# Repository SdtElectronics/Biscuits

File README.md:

# Biscuits 
This repository contains various PCB works for minor projects or auxiliary purposes.

Note: Cloning whole repository for single directory is unnecessary. You can use [DownGit](https://minhaskamal.github.io/DownGit/#/home) to download single directories or file.

## [BBSink](./bbSink/README.md)
USB-PD sink with headers compatible with breadboard. Features a fixed 3.3V supply and one-click voltage selection without incorporating MCUs

## [LCD_Bias_Voltage_Generator](./LCD_Bias_Voltage_Generator/README.md)
Except a 3.3V `DVDD`, LCD panels typically require 4 additional voltages: `AVDD`, `VGH`, `VGL` and `VCOM`. This board employs a simple circuit to generate these 4 voltages from a single 3.3V supply.

## [PCA9685_Breakout](./PCA9685_Breakout/README.md)
Breakout board for PCA9685 I²C to 16-channel PWM controller.

## [BLDC_D28_Drv](./BLDC_D28_Drv/README.md)
Tiny driver stage for mounting on BLDC motors with 28/29mm diameters.

## [CH224Core](./CH224Core/README.md)
Tiny breakout board for CH224K USB-PD sink IC.

## [XPT2046_RTP](./XPT2046_RTP/README.md)
Breakout board for XPT2046 resistive touch screen controller.

## yuyuyu_ant
Antenna for α-wave transmission( XD

## 50P_FPC_FFC_Breakout
Breakout board for FFC/FPC connectors with 50 positions and 0.5mm pitch.

## 40P_FPC_FFC_Breakout
Breakout board for FFC/FPC connectors with 40 positions and 0.5mm pitch.

## 24P_FPC_FFC_Breakout
Breakout board for FFC/FPC connectors with 24 positions and 0.5mm pitch.

## 14P_FPC_FFC_Breakout
Breakout board for FFC/FPC connectors with 14 positions and 0.5mm pitch.

## 9P_FPC_FFC_Breakout
Breakout board for FFC/FPC connectors with 14 positions and 0.5mm or 1mm pitch.

## Licence
All projects contained in this repository, unless otherwise stated, are available under the [CERN OHL-w v2](https://ohwr.org/project/cernohl/wikis/Documents/CERN-OHL-version-2) licence.

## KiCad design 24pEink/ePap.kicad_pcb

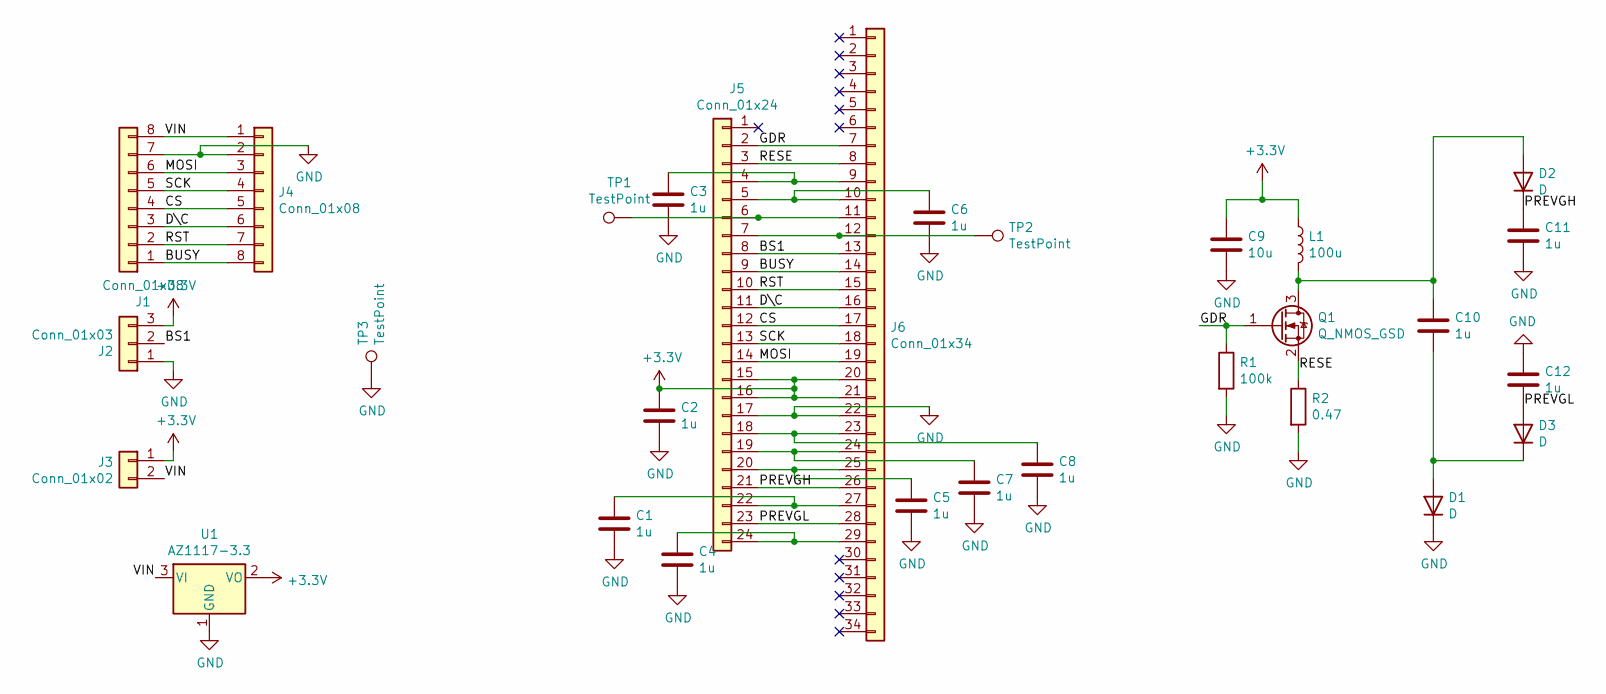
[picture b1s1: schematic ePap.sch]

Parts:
C1, C2, C3, C4, C5, C6, C7, C8, C10, C11, C12: 1u; C_0603_1608Metric_Pad1.05x0.95mm_HandSolder
C9: 10u; C_0603_1608Metric_Pad1.05x0.95mm_HandSolder
D1, D2, D3: D; D_SOD-123
J1: Conn_01x08; TE_0-1734839-8_1x08-1MP_P0.5mm_Horizontal
J2: Conn_01x03; PinHeader_1x03_P2.00mm_Horizontal
J3: Conn_01x02; PinHeader_1x02_P2.00mm_Horizontal
J4: Conn_01x08; PinHeader_1x08_P2.54mm_Vertical
J5: Conn_01x24; TE_2-1734839-4_1x24-1MP_P0.5mm_Horizontal
J6: Conn_01x34; TE_3-1734839-4_1x34-1MP_P0.5mm_Horizontal
L1: 100u; L_Taiyo-Yuden_NR-30xx_HandSoldering
Q1: Q_NMOS_GSD; SOT-23
R1: 100k; R_0805_2012Metric_Pad1.15x1.40mm_HandSolder
R2: 0.47; R_0805_2012Metric_Pad1.15x1.40mm_HandSolder
TP1, TP2: TestPoint; TestPoint_Pad_D1.0mm
TP3: TestPoint; TestPoint_THTPad_D2.5mm_Drill1.2mm
U1: AZ1117-3.3; SOT-223

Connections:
+3V3: C2.1, C9.1, J2.3, J3.1, J5.15, J5.16, J6.20, J6.21, L1.1, U1.2 (VO)
/BS1: J2.2, J5.8, J6.13
/BUSY: J1.1, J4.8, J5.9, J6.14
/CS: J1.4, J4.5, J5.12, J6.17
/D\C: J1.3, J4.6, J5.11, J6.16
/GDR: J5.2, J6.7, Q1.1 (G), R1.1
/MOSI: J1.6, J4.3, J5.14, J6.19
/PREVGH: C11.1, D2.1 (K), J5.21, J6.26
/PREVGL: C12.2, D3.2 (A), J5.23, J6.28
/RESE: J5.3, J6.8, Q1.2 (S), R2.1
/RST: J1.2, J4.7, J5.10, J6.15
/SCK: J1.5, J4.4, J5.13, J6.18
/VIN: J1.8, J3.2, J4.1, U1.3 (VI)
GND: C1.2, C2.2, C3.2, C4.2, C5.2, C6.2, C7.2, C8.2, C9.2, C11.2, C12.1, D1.1 (K), J1.7, J2.1, J4.2, J5.17, J6.22, R1.2, R2.2, TP3.1, U1.1 (GND)
unnamed: C1.1, J5.22, J6.27
unnamed: C3.1, J5.4, J6.9
unnamed: C4.1, J5.24, J6.29
unnamed: C5.1, J5.20, J6.25
unnamed: C6.1, J5.5, J6.10
unnamed: C7.1, J5.19, J6.24
unnamed: C8.1, J5.18, J6.23
unnamed: C10.1, D2.2 (A), L1.2, Q1.3 (D)
unnamed: C10.2, D1.2 (A), D3.1 (K)
unnamed: J5.6, J6.11, TP1.1
unnamed: J5.7, J6.12, TP2.1

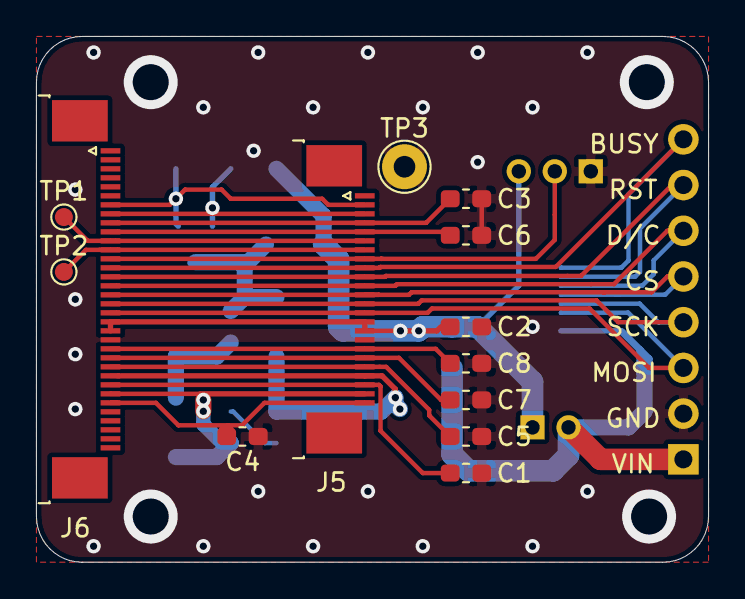
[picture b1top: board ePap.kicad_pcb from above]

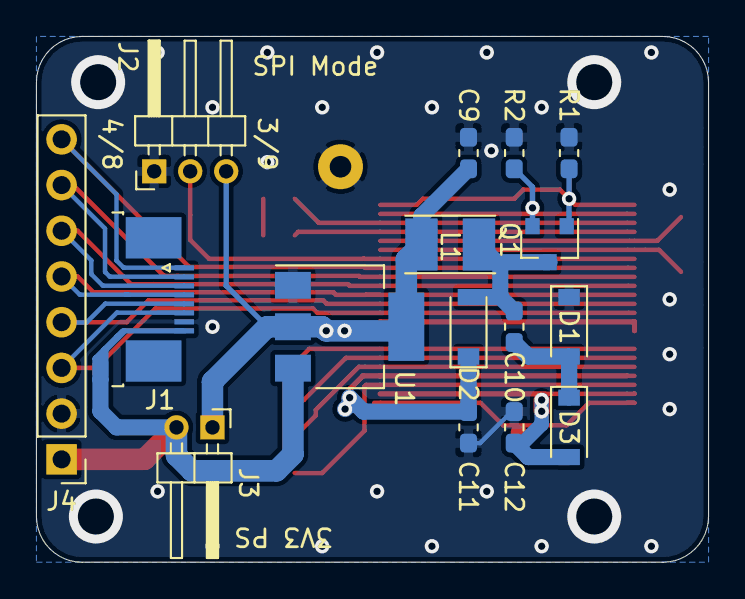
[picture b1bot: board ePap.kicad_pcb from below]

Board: 2 copper layers, 37.3 x 29.2 mm, 29 parts (16 on the bottom side), 25 nets.

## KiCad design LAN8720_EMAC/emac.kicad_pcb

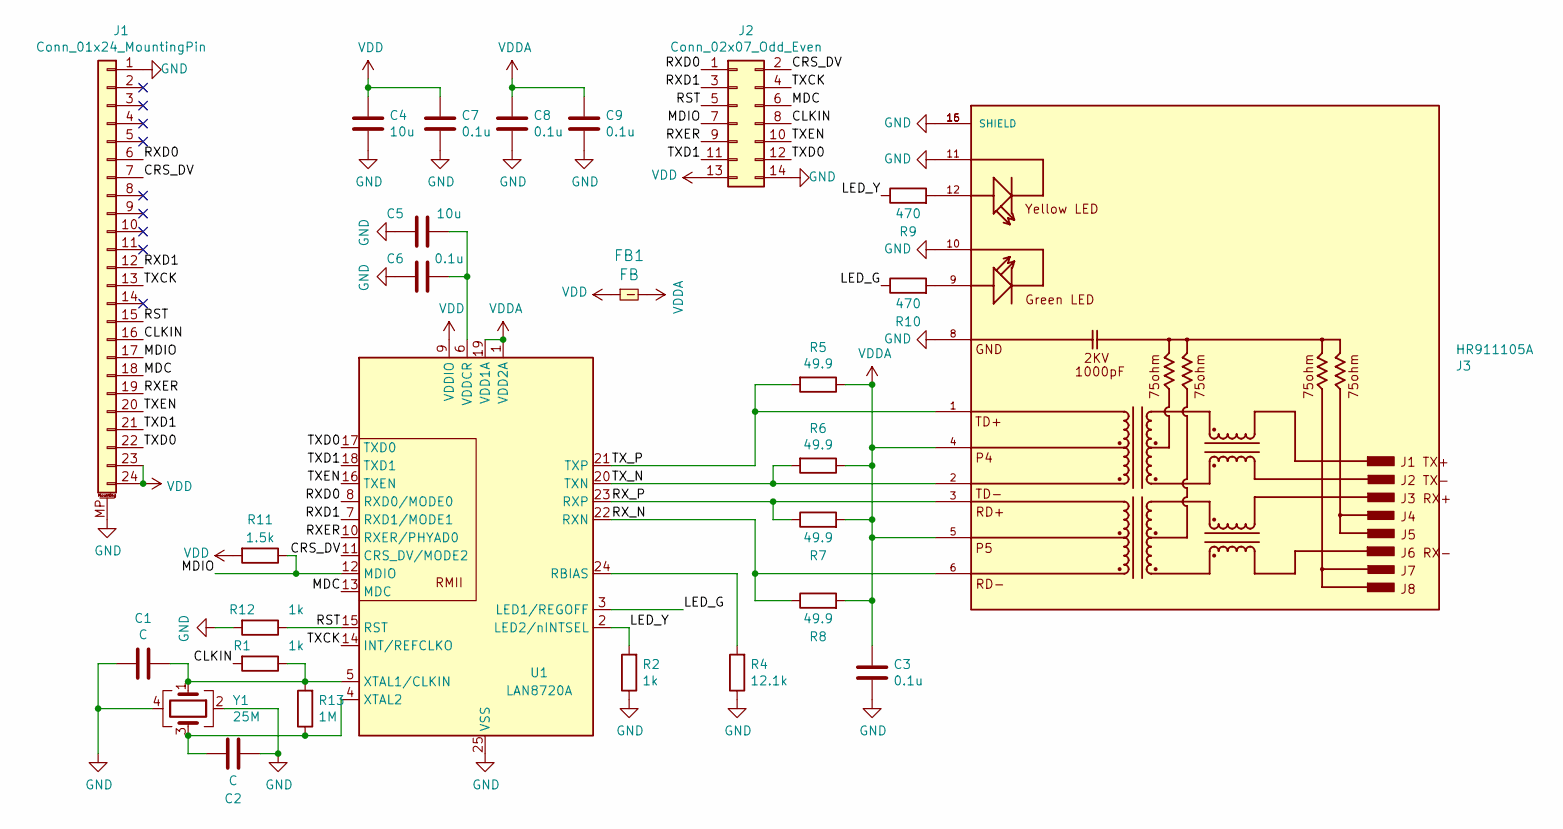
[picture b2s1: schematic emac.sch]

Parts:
C1, C2: C; C_0603_1608Metric
C3, C6, C7, C8, C9: 0.1u; C_0603_1608Metric
C4, C5: 10u; C_0603_1608Metric
FB1: FB; L_0603_1608Metric
J1: Conn_01x24_MountingPin; TE_2-1734839-4_1x24-1MP_P0.5mm_Horizontal
J2: Conn_02x07_Odd_Even; PinHeader_2x07_P2.54mm_Vertical
J3: HR911105A; HANRUN_HR911105A; PARTREV A
R1, R2, R12: 1k; R_0603_1608Metric
R4: 12.1k; R_0603_1608Metric
R5, R6, R7, R8: 49.9; R_0603_1608Metric
R9, R10: 470; R_0603_1608Metric
R11: 1.5k; R_0603_1608Metric
R13: 1M; R_0603_1608Metric
U1: LAN8720A; QFN-24-1EP_4x4mm_P0.5mm_EP2.6x2.6mm
Y1: 25M; Crystal_SMD_3225-4Pin_3.2x2.5mm

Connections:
/CLKIN: J1.16, J2.8, R1.2
/CRS_DV: J1.7, J2.2, U1.11 (CRS_DV/MODE2)
/LED_G: R10.1, U1.3 (LED1/REGOFF)
/LED_Y: R2.2, R9.1, U1.2 (LED2/nINTSEL)
/MDC: J1.18, J2.6, U1.13 (MDC)
/MDIO: J1.17, J2.7, R11.1, U1.12 (MDIO)
/RST: J1.15, J2.5, R12.1, U1.15 (RST)
/RXD0: J1.6, J2.1, U1.8 (RXD0/MODE0)
/RXD1: J1.12, J2.3, U1.7 (RXD1/MODE1)
/RXER: J1.19, J2.9, U1.10 (RXER/PHYAD0)
/RX_N: J3.6, R8.1, U1.22 (RXN)
/RX_P: J3.3, R7.1, U1.23 (RXP)
/TXCK: J1.13, J2.4, U1.14 (INT/REFCLKO)
/TXD0: J1.22, J2.12, U1.17 (TXD0)
/TXD1: J1.21, J2.11, U1.18 (TXD1)
/TXEN: J1.20, J2.10, U1.16 (TXEN)
/TX_N: J3.2, R6.2, U1.20 (TXN)
/TX_P: J3.1, R5.2, U1.21 (TXP)
GND: C1.1, C2.2, C3.2, C4.2, C5.1, C6.1, C7.2, C8.2, C9.2, J1.1, J1.MP (MountPin), J2.14, J3.8, J3.10, J3.11, J3.15 (SHIELD), J3.16 (SHIELD), R2.1, R4.1, R12.2, U1.25 (VSS), Y1.2, Y1.4
unnamed: C1.2, R1.1, R13.2, U1.5 (XTAL1/CLKIN), Y1.1
unnamed: C2.1, R13.1, U1.4 (XTAL2), Y1.3
unnamed: C5.2, C6.2, U1.6 (VDDCR)
unnamed: J3.9, R10.2
unnamed: J3.12, R9.2
unnamed: R4.2, U1.24 (RBIAS)
VDD: C4.1, C7.1, FB1.1, J1.23, J1.24, J2.13, R11.2, U1.9 (VDDIO)
VDDA: C3.1, C8.1, C9.1, FB1.2, J3.4, J3.5, R5.1, R6.1, R7.2, R8.2, U1.1 (VDD2A), U1.19 (VDD1A)

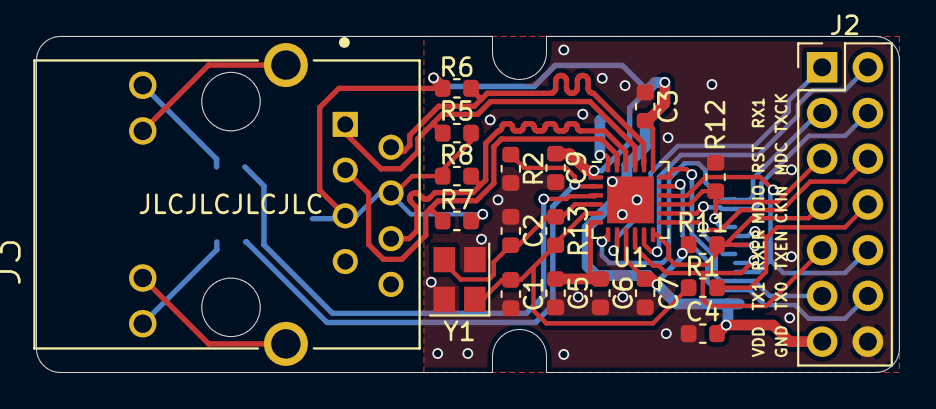
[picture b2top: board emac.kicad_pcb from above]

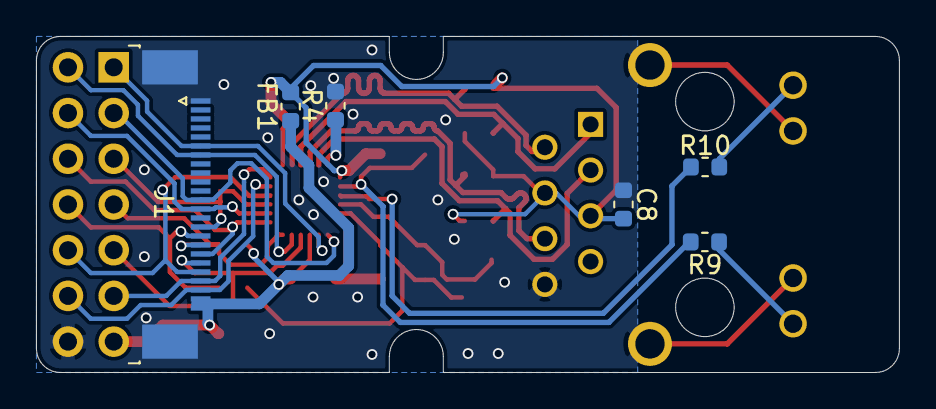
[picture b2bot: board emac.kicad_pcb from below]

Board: 2 copper layers, 47.9 x 18.7 mm, 27 parts (6 on the bottom side), 27 nets.

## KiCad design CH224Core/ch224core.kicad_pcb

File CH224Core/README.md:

# CH224Core
Tiny breakout board for CH224K USB-PD sink IC.

## Highlights:
* Supports dynamically programmable 5V, 9V, 12V, 15V, 20V output
* Compact outline in only 15x10 mm
* Breadboard-friendly pitch

## Status:
Fully verified.

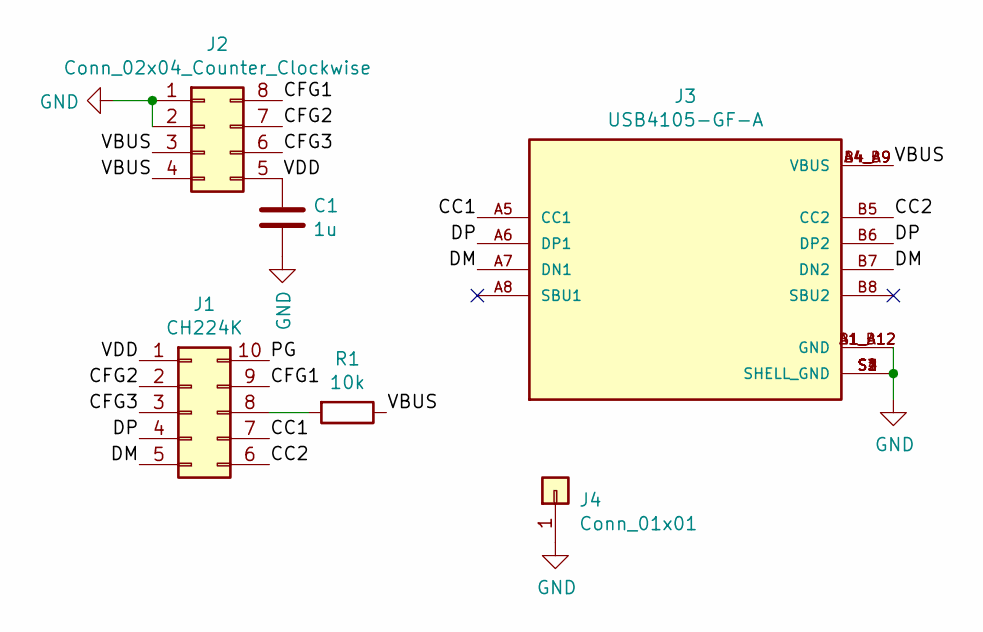
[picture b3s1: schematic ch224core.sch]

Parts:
C1: 1u; C_0603_1608Metric
J1: CH224K; SSOP-10-1.0pitch
J2: Conn_02x04_Counter_Clockwise; DIP-8_W12.7mm
J3: USB4105-GF-A; GCT_USB4105-GF-A; PARTREV A3
J4: Conn_01x01; SM-PAD_2x3mm
R1: 10k; R_0603_1608Metric

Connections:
/CC1: J1.7, J3.A5 (CC1)
/CC2: J1.6, J3.B5 (CC2)
/CFG1: J1.9, J2.8
/CFG2: J1.2, J2.7
/CFG3: J1.3, J2.6
/DM: J1.5, J3.A7 (DN1), J3.B7 (DN2)
/DP: J1.4, J3.A6 (DP1), J3.B6 (DP2)
/PG: J1.10
/VBUS: J2.3, J2.4, J3.A4_B9 (VBUS), J3.B4_A9 (VBUS), R1.1
/VDD: C1.1, J1.1, J2.5
GND: C1.2, J2.1, J2.2, J3.A1_B12 (GND), J3.B1_A12 (GND), J3.S1 (SHELL_GND), J3.S2 (SHELL_GND), J3.S3 (SHELL_GND), J3.S4 (SHELL_GND), J4.1
unnamed: J1.8, R1.2

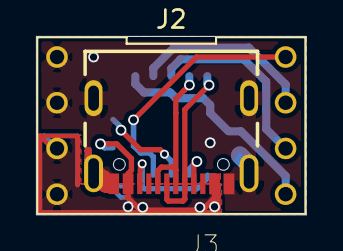
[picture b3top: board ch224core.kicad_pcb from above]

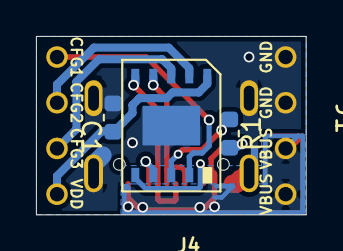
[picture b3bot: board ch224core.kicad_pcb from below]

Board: 2 copper layers, 15.0 x 9.9 mm, 6 parts (4 on the bottom side), 11 nets.

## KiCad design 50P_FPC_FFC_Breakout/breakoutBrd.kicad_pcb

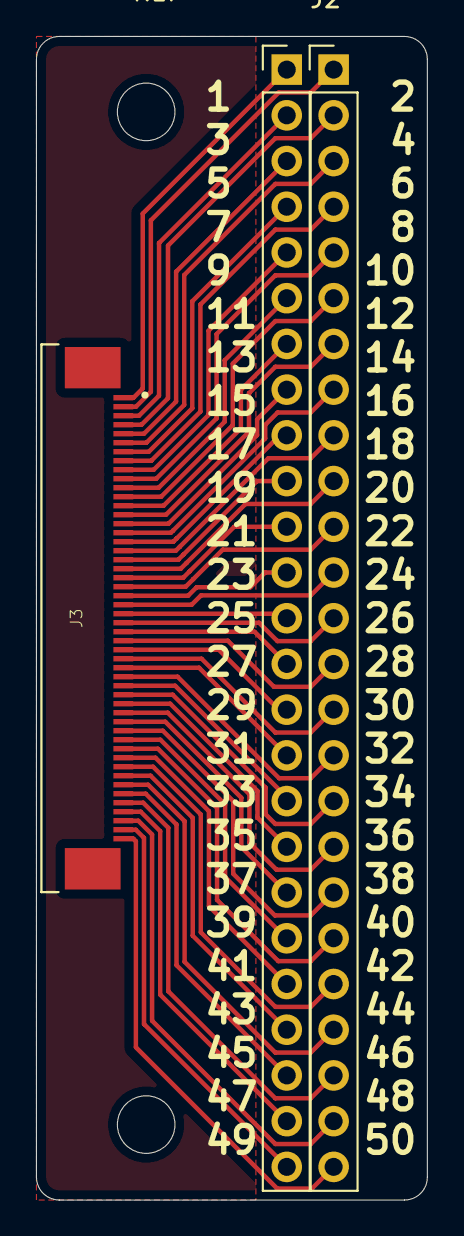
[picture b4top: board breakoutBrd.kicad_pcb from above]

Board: 2 copper layers, 21.7 x 64.6 mm, 3 parts (0 on the bottom side), 50 nets.

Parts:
J1, J2: Conn_01x25; PinHeader_1x25_P2.54mm_Vertical
J3: Conn50; TE_5-1734592-0

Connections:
unnamed: J1.1, J3.2
unnamed: J1.2, J3.4
unnamed: J1.3, J3.6
unnamed: J1.4, J3.8
unnamed: J1.5, J3.10
unnamed: J1.6, J3.12
unnamed: J1.7, J3.14
unnamed: J1.8, J3.16
unnamed: J1.9, J3.18
unnamed: J1.10, J3.20
unnamed: J1.11, J3.22
unnamed: J1.12, J3.24
unnamed: J1.13, J3.26
unnamed: J1.14, J3.28
unnamed: J1.15, J3.30
unnamed: J1.16, J3.32
unnamed: J1.17, J3.34
unnamed: J1.18, J3.36
unnamed: J1.19, J3.38
unnamed: J1.20, J3.40
unnamed: J1.21, J3.42
unnamed: J1.22, J3.44
unnamed: J1.23, J3.46
unnamed: J1.24, J3.48
unnamed: J1.25, J3.50
unnamed: J2.1, J3.1
unnamed: J2.2, J3.3
unnamed: J2.3, J3.5
unnamed: J2.4, J3.7
unnamed: J2.5, J3.9
unnamed: J2.6, J3.11
unnamed: J2.7, J3.13
unnamed: J2.8, J3.15
unnamed: J2.9, J3.17
unnamed: J2.10, J3.19
unnamed: J2.11, J3.21
unnamed: J2.12, J3.23
unnamed: J2.13, J3.25
unnamed: J2.14, J3.27
unnamed: J2.15, J3.29
unnamed: J2.16, J3.31
unnamed: J2.17, J3.33
unnamed: J2.18, J3.35
unnamed: J2.19, J3.37
unnamed: J2.20, J3.39
unnamed: J2.21, J3.41
unnamed: J2.22, J3.43
unnamed: J2.23, J3.45
unnamed: J2.24, J3.47
unnamed: J2.25, J3.49

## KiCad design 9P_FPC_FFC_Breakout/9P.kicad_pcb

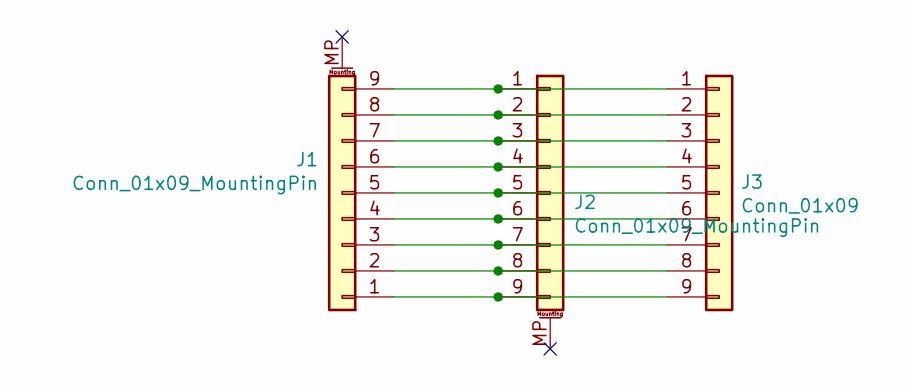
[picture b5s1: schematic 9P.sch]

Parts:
J1: Conn_01x09_MountingPin; TE_0-1734839-9_1x09-1MP_P0.5mm_Horizontal
J2: Conn_01x09_MountingPin; TE_84952-9_1x09-1MP_P1.0mm_Horizontal
J3: Conn_01x09; PinHeader_1x09_P2.54mm_Vertical

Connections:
unnamed: J1.1, J2.9, J3.9
unnamed: J1.2, J2.8, J3.8
unnamed: J1.3, J2.7, J3.7
unnamed: J1.4, J2.6, J3.6
unnamed: J1.5, J2.5, J3.5
unnamed: J1.6, J2.4, J3.4
unnamed: J1.7, J2.3, J3.3
unnamed: J1.8, J2.2, J3.2
unnamed: J1.9, J2.1, J3.1

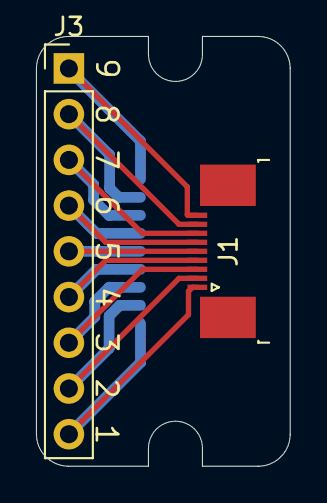
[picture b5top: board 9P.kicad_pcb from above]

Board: 2 copper layers, 14.1 x 23.9 mm, 3 parts (1 on the bottom side), 9 nets.

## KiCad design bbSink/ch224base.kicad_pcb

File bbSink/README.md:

# BBSink
USB-PD sink with headers compatible with breadboard. Features a fixed 3.3V supply and one-click voltage selection without incorporating MCUs. 

## Highlights
* Dual channel supplies with one fixed 3.3V output and one 5V / 9V / 12V / 15V / 20V configurable output
* User-friendly operation: one-click voltage selection and LED indicators
* Incorporates no MCU and is therefore cheap and programming-free

## Instructions on Building
This design consists two PCBs: a base board and a CH224K Core board which owns [its separate directory](https://github.com/SdtElectronics/Biscuits/tree/master/CH224Core). The layout file [ch224baseProdt](https://github.com/SdtElectronics/Biscuits/blob/master/bbSink/ch224baseProdt.kicad_pcb) in this folder combines two PCBs together so they can be (ordered and) manufactured at once.

The layout of this board took special consideration on soldering: All footprints with small pitches are arranged on the bottom side so they can be soldered easily with paste and heat guns or PTC heating tables. Components on the top side should be dealt afterwards.

## Outputs
The primary outputs are two 2x4 pin headers compatible with breadboards. Headers on left supply voltage sunk from the USB-C port while headers on right supply a fixed 3.3V output. In both sides, positive terminal is left column and GND is on right.

Besides the pin headers, the sunk voltage is also supplied with a pad for connectors of 5.08mm pitches. On the right side, if the pad for external regulator is unused, it can also act as a 3.3V supply.

Below the pad for fuse, there is another pin header. This is connected to the internal 5V regulator of `MPM3620`. Its load characteristic is not clearly specified by the datasheet so better not to rely on it.

## 3V3 Step Down Circuitry
There are 3 options to generate a 3.3V supply for on-board circuits and output:
* A compact DC-DC circuit employing `MPM3620` synchronous converter with integrated inductor. This requires `R4` - `R7` being soldered.
* Any LDO in SOT-223 package with pin assignment compatible with `LM1117`. Do beware of the voltage rating of the LDO you choose: `LM1117` only tolerates input up to 15V thus it cannot be operated safely when sinking 20V. An alternative with higher rating is `NCP1117`.
* An external regulator can be connected to the board with a 78XX compatible pad at `REG_EXT`. 

You can opt into any of the three above but don't use them in parallel. That would be most unlikely to increase the output current.

## Notes
* The LEDs indicate the selected voltage required by the sink IC, rather than the actual output voltage.
* `CH224K` claims it also supports BC1.2 protocol, which I have barely heard of it. It seems to be a common base of a family of protocols including QC2.0. I have tested this board with a QC2.0 charger for my Nokia 7 Plus, and it can sink 5V, 9V and 12V as well.
* If you don't want a fuse just short it with `JP1`. Or you can solder something interesting on it e.g. a SMD switch.

## Known Issues
The output voltage on power up is undetermined until a button is pressed, although it should be 9V in most of the time. I have designed a RC pulse generator to set the default voltage level to 5V but it failed miserably: the capacitor `C1` is either too small to trigger the logic components, or too large that the state can't be hold after being triggered. Therefore, the pad for `C1` should be left unconnected for now. Someday I will fix this or maybe never, cause I'm too lazy to devote to such minor functionality...

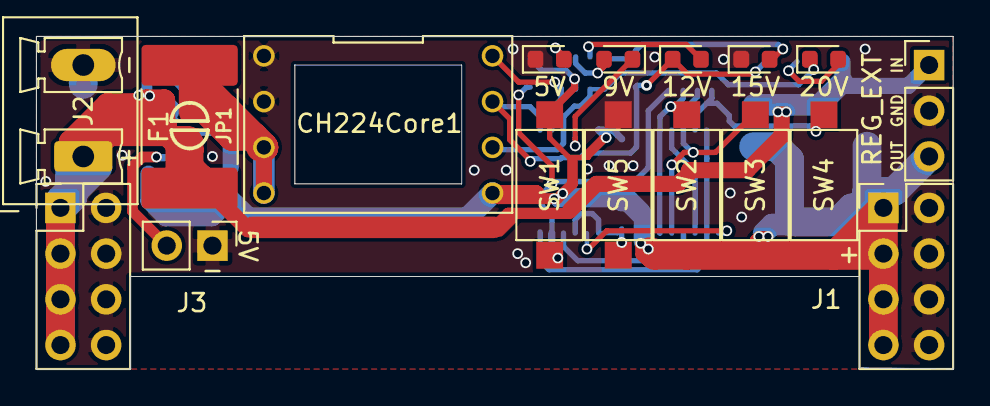
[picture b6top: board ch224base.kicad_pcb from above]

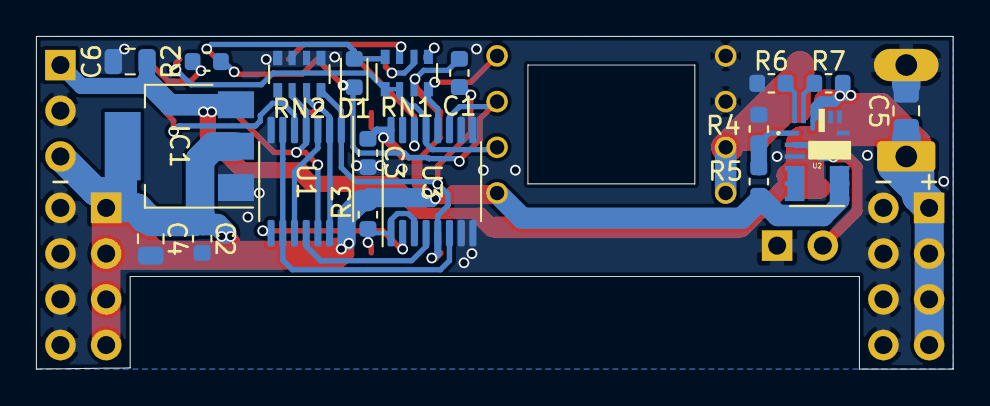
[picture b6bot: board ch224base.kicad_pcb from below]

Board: 2 copper layers, 50.9 x 18.5 mm, 37 parts (19 on the bottom side), 27 nets.

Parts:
5V, 9V, 12V, 15V, 20V: LED; LED_0603_1608Metric
5V#2: Conn_01x02; PinHeader_1x02_P2.54mm_Vertical
C1, C2, C3: 1u; C_0603_1608Metric
C4: 22u; C_0805_2012Metric
C5: 47u; C_0805_2012Metric
C6: 10u; C_0805_2012Metric
CH224Core1: Conn_02x04_Counter_Clockwise; DIP-8_W12.7mm
D1: D; D_0603_1608Metric
F1: Fuse; Fuse_2920_7451Metric_Castellated
IC1: NCP1117; SOT-223
J1, J3: Conn_02x04_Counter_Clockwise; PinHeader_2x04_P2.54mm_Vertical
J2: Conn_01x02; PhoenixContact_MCV_1,5_2-G-5.08_1x02_P5.08mm_Vertical
JP1: Jumper; SOLDER-JUMPER_1-WAY
R2: 1.5k; R_0603_1608Metric
R3, R7: 4.7k; R_0603_1608Metric
R4: 51k; R_0603_1608Metric
R5: 160k; R_0603_1608Metric
R6: 56k; R_0603_1608Metric
REG_EXT: Conn_01x03; PinHeader_1x03_P2.54mm_Vertical
RN1, RN2: R_Pack04; R_Array_Convex_4x0603
SW1, SW2, SW3, SW4, SW5: SW_DIP_x01; SW_SPST_CK_RS282G05A3
U1: 74LS32; TSSOP-14_4.4x5mm_P0.65mm
U2: MPM3620GQV-Z; CONV_MPM3620AGQV-P
U3: 74LVC161; TSSOP-16_4.4x5mm_P0.65mm

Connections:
+3V3: C1.2, C2.2, C3.2, C4.2, CH224Core1.5, IC1.2, IC1.4, J1.1, J1.2, J1.3, J1.4, R3.1, R5.1, REG_EXT.3, RN1.7, SW1.1, SW2.1, SW3.1, SW4.1, U1.14, U2.7, U2.8, U2.9, U2.20, U3.16
/CFG1: CH224Core1.8, RN1.8, U3.12
/CFG2: 12V.1, CH224Core1.7, D1.1, R2.1, U3.11
/CFG3: 20V.1, CH224Core1.6, RN1.5, RN1.6, U3.13
/LED: 9V.1, U3.14
/V5: C1.1, RN2.8, SW1.2, U1.1, U3.5
/V9: R3.2, SW5.1, U3.1, U3.3
/V12: RN2.7, SW2.2, U1.2, U1.13
/V15: RN2.6, SW3.2, U1.4, U1.12
/V20: RN2.5, SW4.2, U1.5
/VBUS: C5.2, C6.2, F1.1, IC1.3, J2.1, J3.1, J3.2, J3.3, J3.4, JP1.1, R7.2, REG_EXT.1, U2.16
GND: 5V.1, 5V#2.1, 15V.1, C2.1, C3.1, C4.1, C5.1, C6.1, CH224Core1.1, CH224Core1.2, IC1.1, J1.5, J1.6, J1.7, J1.8, J2.2, J3.5, J3.6, J3.7, J3.8, R4.1, R6.2, REG_EXT.2, RN2.1, RN2.2, RN2.3, RN2.4, SW5.2, U1.7, U2.3, U2.12, U2.13, U2.14, U3.7, U3.8, U3.9, U3.10
unnamed: 5V.2, RN1.1
unnamed: 5V#2.2, U2.2
unnamed: 9V.2, RN1.2
unnamed: 12V.2, RN1.3
unnamed: 15V.2, D1.2, RN1.4
unnamed: 20V.2, R2.2
unnamed: CH224Core1.3, CH224Core1.4, F1.2, JP1.2
unnamed: R4.2, R5.2, U2.1
unnamed: R6.1, U2.18
unnamed: R7.1, U2.17
unnamed: U1.6, U1.9, U3.6
unnamed: U1.8, U3.2
unnamed: U1.3, U1.10
unnamed: U1.11, U3.4
unnamed: U2.4, U2.5, U2.6, U2.19

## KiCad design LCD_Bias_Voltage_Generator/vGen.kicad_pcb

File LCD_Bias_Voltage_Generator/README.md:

# LCD Bias Voltage Generator
Except a 3.3V `DVDD`, LCD panels typically require 4 additional voltages: `AVDD`, `VGH`, `VGL` and `VCOM`. This board employs a simple circuit to generate these 4 voltages from a single 3.3V supply.

## AVDD Generation 
`AVDD` is generated by a step-up DC-DC convertor IC [AP3019](https://pdf.dzsc.com/88888/200712310948474.pdf). The output voltage is set by `AVDD=0.2*(1+R3/R4)` . With default values set in the schematic, a 10.8V `AVDD` is generated.

## VGH and VGL Generation
Both `VGH` and `VGL` are generated via charge pumps and regulated by zener diodes. Setting output voltage can be accomplished by replacing zener diodes accordingly, but no higher than 20V. With default diodes chosen in the schematic, a 15V `VGH` and a -6.8V `VGL` are generated.

## VCOM Generation
`VCOM` is generated by dividing `AVDD` output. This board provides two types of divider: An adjustable divider with a potentiometer `RV1` and a fixed one with two resistors `R2` and `R1`. For example, if you want a (approximately) 3.8V `VCOM` with 10.8V `AVDD`, you can set `R2` to 7.5kΩ and `R1` to 13kΩ.

## Status
Verified with components values set in the schematic.

## Notes 
Step-up DC-DC convertor IC alternatives: 
Theoretically all Step-up convertors in sot23-6(sot23-5) packages with compatible pin assignment can be replacements, but special care should be paid on the internal references of ICs. If reference voltage is not 0.2V, the above formula should not be applied directly. One candidate with 0.2V ref is [SY7201](http://www.applelogic.org/files/SY7201A.pdf) (untested).

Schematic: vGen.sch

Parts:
C1: 10u; C_0805_2012Metric_Pad1.15x1.40mm_HandSolder
C2: 102; C_0603_1608Metric_Pad1.05x0.95mm_HandSolder
C3: NC; C_0603_1608Metric_Pad1.05x0.95mm_HandSolder
C4, C6, C7, C8, C9, C10, C11: 104; C_0603_1608Metric_Pad1.05x0.95mm_HandSolder
C5: 10uF; C_0805_2012Metric_Pad1.15x1.40mm_HandSolder
D1: SS14; D_SMA
D2, D3: BAT54S; SOT-23
D4: 1N4744; D_1206_3216Metric
D5: 1N4736; D_1206_3216Metric
J1: Conn_01x06; PinHeader_1x06_P2.54mm_Vertical
L1: 10uH; L_Taiyo-Yuden_MD-4040
R1, R2: R; R_0603_1608Metric_Pad1.05x0.95mm_HandSolder
R3: 51k; R_0603_1608Metric_Pad1.05x0.95mm_HandSolder
R4: 1k; R_0603_1608Metric_Pad1.05x0.95mm_HandSolder
R5, R6: 1.5k; R_0603_1608Metric_Pad1.05x0.95mm_HandSolder
R7: 20k; R_0603_1608Metric_Pad1.05x0.95mm_HandSolder
R8, R9: 47k; R_0603_1608Metric_Pad1.05x0.95mm_HandSolder
RV1: R_POT; Potentiometer_Bourns_TC33X_Vertical
U1: AP3019AKTR-G1

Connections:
/COM: J1.2, R1.1, R2.1, RV1.2
/GH: C10.1, D4.1, J1.4, R5.1, R8.1
/GL: C11.1, D5.2, J1.5, R6.1, R9.1
/VIN: C1.1, C2.1, J1.1, L1.1, U1.4 (CTRL), U1.6 (VIN)
/VS: C3.1, C5.1, C9.1, D1.1, D2.1, J1.3, R1.2, R3.1, R7.1, RV1.3, U1.5 (VOUT)
GND: C1.2, C2.2, C5.2, C7.2, C8.2, C9.2, C10.2, C11.2, D3.2, D4.2, D5.1, J1.6, R2.2, R4.2, R7.2, R8.2, R9.2, RV1.1, U1.2 (GND)
unnamed: C3.2, R3.2, R4.1, U1.3 (FB)
unnamed: C4.1, D2.3
unnamed: C4.2, C6.2, D1.2, L1.2, U1.1 (SW)
unnamed: C6.1, D3.3
unnamed: C7.1, D2.2, R5.2
unnamed: C8.1, D3.1, R6.2

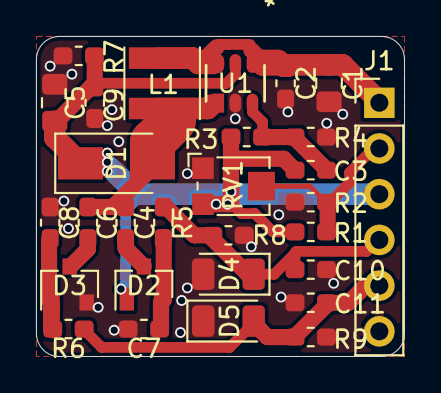
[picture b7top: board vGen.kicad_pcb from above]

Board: 2 copper layers, 20.4 x 17.8 mm, 29 parts (0 on the bottom side), 12 nets.

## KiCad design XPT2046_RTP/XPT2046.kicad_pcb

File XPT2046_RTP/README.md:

# XPT2046_RTP
Breakout board for XPT2046 resistive touch screen controller.

## Status 
Manufactured but untested.

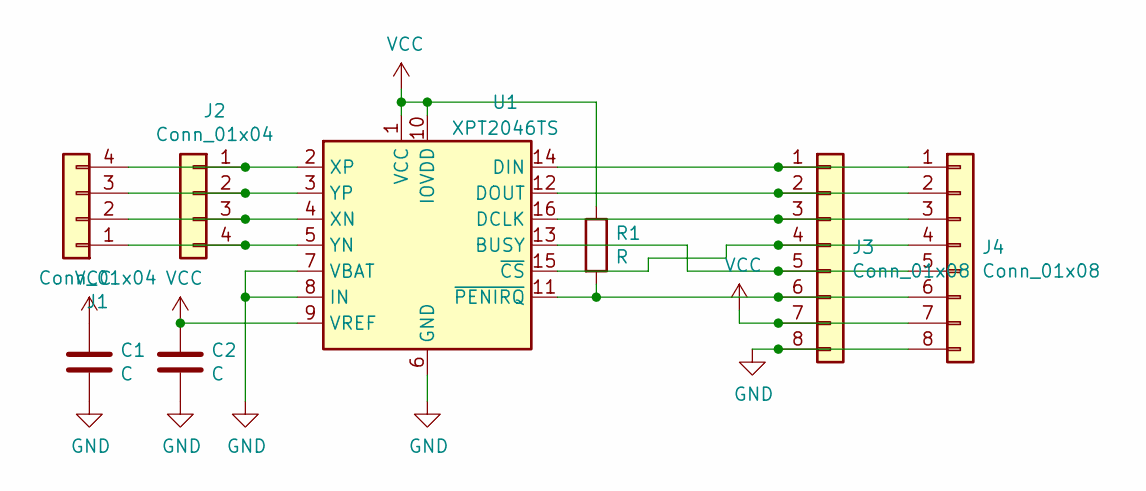
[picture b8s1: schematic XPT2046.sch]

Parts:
C1, C2: C; C_0603_1608Metric_Pad1.05x0.95mm_HandSolder
J1: Conn_01x04; MOLEX_54548-0471
J2: Conn_01x04; PinHeader_1x04_P2.54mm_Vertical
J3: Conn_01x08; PinHeader_1x08_P2.54mm_Vertical
J4: Conn_01x08; TE_0-1734839-8_1x08-1MP_P0.5mm_Horizontal
R1: R; R_0603_1608Metric_Pad1.05x0.95mm_HandSolder
U1: XPT2046TS; TSSOP-16_4.4x5mm_P0.65mm

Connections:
GND: C1.2, C2.2, J3.8, J4.8, U1.6 (GND), U1.7 (VBAT), U1.8 (IN)
unnamed: J1.1, J2.4, U1.5 (YN)
unnamed: J1.2, J2.3, U1.4 (XN)
unnamed: J1.3, J2.2, U1.3 (YP)
unnamed: J1.4, J2.1, U1.2 (XP)
unnamed: J3.1, J4.1, U1.14 (DIN)
unnamed: J3.2, J4.2, U1.12 (DOUT)
unnamed: J3.3, J4.3, U1.16 (DCLK)
unnamed: J3.4, J4.4, U1.15 (~CS)
unnamed: J3.5, J4.5, U1.13 (BUSY)
unnamed: J3.6, J4.6, R1.2, U1.11 (~PENIRQ)
VCC: C1.1, C2.1, J3.7, J4.7, R1.1, U1.1 (VCC), U1.9 (VREF), U1.10 (IOVDD)

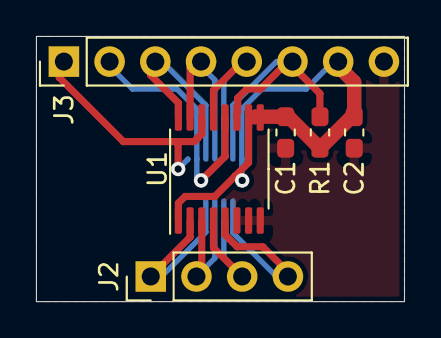
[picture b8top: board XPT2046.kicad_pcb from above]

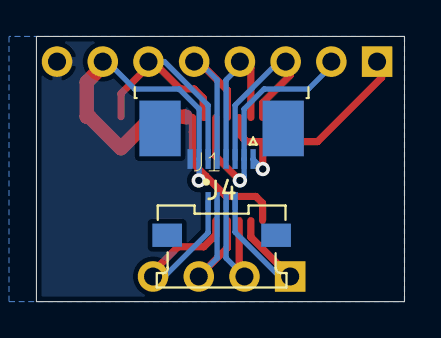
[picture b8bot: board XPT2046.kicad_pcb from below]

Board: 2 copper layers, 20.4 x 14.7 mm, 8 parts (2 on the bottom side), 12 nets.

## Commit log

2021-01-31 add 50P FPC/FFC Breakout Board
2021-02-02 add README
2021-02-04 add breakoutBrdF1C
2021-02-06 add LCD_Bias_Voltage_Generator
2021-02-12 add README for LCD_Bias_Voltage_Generator
2021-02-12 add XPT2046_RTP
2021-02-20 add  14P_FPC_FFC_Breakout
2021-02-23 add BLDC_D28_Drv
2021-02-26 add 24P_FPC_FFC_Breakout
2021-03-01 add pogo_tester
2021-03-09 add PCA9685_Breakout
2021-04-11 add CH224Core
2021-04-13 add docs for CH244KCore
2021-04-16 add 24P_Dual_hetro
2021-04-16 update CH224Core PCB
2021-04-19 add bbSink
2021-04-27 update status for PCA9685_Breakout and BLDC_D28_Drv
2021-05-01 update docs
2021-05-01 add gallery
2021-05-19 add licence
2021-07-02 add 9P_FPC_FFC_Breakout
2021-10-13 add yuyuyu_ant
2021-11-11 add 40P_FPC_FFC_Breakout
2021-11-21 add preview to README
2021-12-15 add LAN8720_EMAC
2022-03-24 add 24pEink

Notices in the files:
parts and their libraries:
Copyright 2016 Accelerated Designs. All rights reserved.
